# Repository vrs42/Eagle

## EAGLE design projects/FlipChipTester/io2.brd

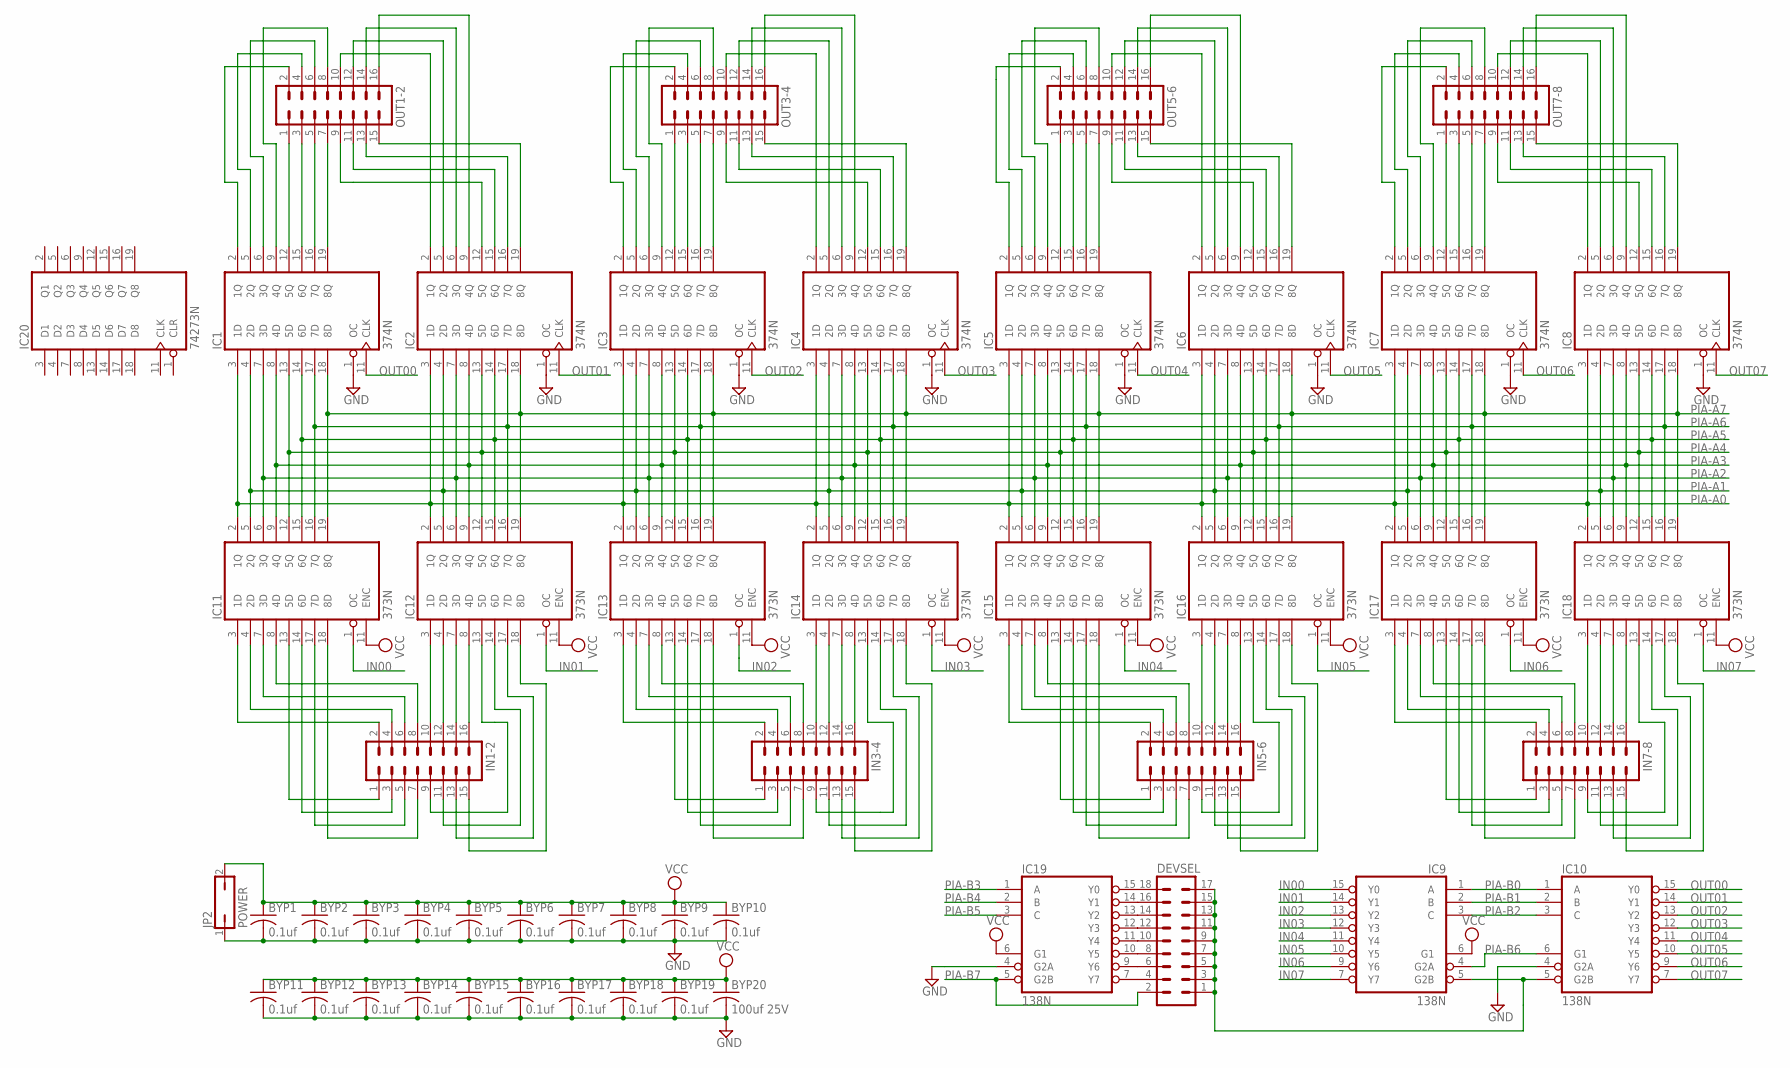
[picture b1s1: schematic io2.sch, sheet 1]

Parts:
BYP1, BYP2, BYP3, BYP4, BYP5, BYP6, BYP7, BYP8, BYP9, BYP10, BYP11, BYP12, BYP13, BYP14, BYP15, BYP16, BYP17, BYP18, BYP19: 0.1uf; C050-025X075
BYP20: 100uf 25V; C150-064X183
DEVSEL: MA09-2
IC1, IC2, IC3, IC4, IC5, IC6, IC7, IC8: 374N; DIL20
IC9, IC10, IC19: 138N; DIL16
IC11, IC12, IC13, IC14, IC15, IC16, IC17, IC18: 373N; DIL20
IC20: 74273N; DIL20
IN1-2, IN3-4, IN5-6, IN7-8: MA08-2
JP2: POWER; JP1
OUT1-2, OUT3-4, OUT5-6, OUT7-8: MA08-2

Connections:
GND: BYP1.2, BYP2.2, BYP3.2, BYP4.2, BYP5.2, BYP6.2, BYP7.2, BYP8.2, BYP9.2, BYP10.2, BYP11.2, BYP12.2, BYP13.2, BYP14.2, BYP15.2, BYP16.2, BYP17.2, BYP18.2, BYP19.2, BYP20.2, IC1.1 (OC), IC1.10 (GND), IC2.1 (OC), IC2.10 (GND), IC3.1 (OC), IC3.10 (GND), IC4.1 (OC), IC4.10 (GND), IC5.1 (OC), IC5.10 (GND), IC6.1 (OC), IC6.10 (GND), IC7.1 (OC), IC7.10 (GND), IC8.1 (OC), IC8.10 (GND), IC9.8 (GND), IC10.4 (G2A), IC10.8 (GND), IC11.10 (GND), IC12.10 (GND), IC13.10 (GND), IC14.10 (GND), IC15.10 (GND), IC16.10 (GND), IC17.10 (GND), IC18.10 (GND), IC19.4 (G2A), IC19.8 (GND), IC20.10 (GND), JP2.1; also elsewhere on the board
IN00: IC9.15 (Y0), IC11.1 (OC)
IN01: IC9.14 (Y1), IC12.1 (OC)
IN02: IC9.13 (Y2), IC13.1 (OC)
IN03: IC9.12 (Y3), IC14.1 (OC)
IN04: IC9.11 (Y4), IC15.1 (OC)
IN05: IC9.10 (Y5), IC16.1 (OC)
IN06: IC9.9 (Y6), IC17.1 (OC)
IN07: IC9.7 (Y7), IC18.1 (OC)
unnamed: IC12.3 (1D), IN1-2.10
unnamed: IC12.4 (2D), IN1-2.12
unnamed: DEVSEL.18, IC19.15 (Y0)
unnamed: DEVSEL.16, IC19.14 (Y1)
unnamed: DEVSEL.14, IC19.13 (Y2)
unnamed: DEVSEL.12, IC19.12 (Y3)
unnamed: IC12.7 (3D), IN1-2.14
unnamed: IC12.8 (4D), IN1-2.16
unnamed: IC11.8 (4D), IN1-2.8
unnamed: IC11.7 (3D), IN1-2.6
unnamed: IC11.4 (2D), IN1-2.4
unnamed: IC11.3 (1D), IN1-2.2
unnamed: IC11.13 (5D), IN1-2.1
unnamed: IC11.14 (6D), IN1-2.3
unnamed: IC11.17 (7D), IN1-2.5
unnamed: IC11.18 (8D), IN1-2.7
unnamed: IC12.13 (5D), IN1-2.9
unnamed: IC12.14 (6D), IN1-2.11
unnamed: IC12.17 (7D), IN1-2.13
unnamed: IC12.18 (8D), IN1-2.15
unnamed: DEVSEL.10, IC19.11 (Y4)
unnamed: DEVSEL.8, IC19.10 (Y5)
unnamed: DEVSEL.6, IC19.9 (Y6)
unnamed: DEVSEL.4, IC19.7 (Y7)
unnamed: DEVSEL.1, DEVSEL.3, DEVSEL.5, DEVSEL.7, DEVSEL.9, DEVSEL.11, DEVSEL.13, DEVSEL.15, DEVSEL.17, IC9.5 (G2B), IC10.5 (G2B)
unnamed: IC5.2 (1Q), OUT5-6.2
unnamed: IC18.8 (4D), IN7-8.16
unnamed: IC18.3 (1D), IN7-8.10
unnamed: IC14.3 (1D), IN3-4.10
unnamed: IC14.4 (2D), IN3-4.12
unnamed: IC14.7 (3D), IN3-4.14
unnamed: IC14.8 (4D), IN3-4.16
unnamed: IC3.12 (5Q), OUT3-4.1
unnamed: IC3.15 (6Q), OUT3-4.3
unnamed: IC3.16 (7Q), OUT3-4.5
unnamed: IC3.19 (8Q), OUT3-4.7
unnamed: IC13.3 (1D), IN3-4.2
unnamed: IC13.4 (2D), IN3-4.4
unnamed: IC13.7 (3D), IN3-4.6
unnamed: IC13.8 (4D), IN3-4.8
unnamed: IC14.13 (5D), IN3-4.9
unnamed: IC14.14 (6D), IN3-4.11
unnamed: IC14.17 (7D), IN3-4.13
unnamed: IC14.18 (8D), IN3-4.15
unnamed: IC13.13 (5D), IN3-4.1
unnamed: IC13.14 (6D), IN3-4.3
unnamed: IC13.17 (7D), IN3-4.5
unnamed: IC13.18 (8D), IN3-4.7
unnamed: IC3.5 (2Q), OUT3-4.4
unnamed: IC3.6 (3Q), OUT3-4.6
unnamed: IC3.2 (1Q), OUT3-4.2
unnamed: IC3.9 (4Q), OUT3-4.8
unnamed: IC1.12 (5Q), OUT1-2.1
unnamed: IC1.15 (6Q), OUT1-2.3
unnamed: IC1.16 (7Q), OUT1-2.5
unnamed: IC1.19 (8Q), OUT1-2.7
unnamed: IC1.2 (1Q), OUT1-2.2
unnamed: IC1.5 (2Q), OUT1-2.4
unnamed: IC1.6 (3Q), OUT1-2.6
unnamed: IC1.9 (4Q), OUT1-2.8
unnamed: IC2.19 (8Q), OUT1-2.15
unnamed: IC2.16 (7Q), OUT1-2.13
unnamed: IC2.15 (6Q), OUT1-2.11
unnamed: IC2.12 (5Q), OUT1-2.9
unnamed: IC2.2 (1Q), OUT1-2.10
unnamed: IC2.5 (2Q), OUT1-2.12
unnamed: IC2.6 (3Q), OUT1-2.14
unnamed: IC2.9 (4Q), OUT1-2.16
unnamed: IC4.2 (1Q), OUT3-4.10
unnamed: IC4.5 (2Q), OUT3-4.12
unnamed: IC4.6 (3Q), OUT3-4.14
unnamed: IC4.9 (4Q), OUT3-4.16
unnamed: IC4.19 (8Q), OUT3-4.15
unnamed: IC4.16 (7Q), OUT3-4.13
unnamed: IC4.15 (6Q), OUT3-4.11
unnamed: IC4.12 (5Q), OUT3-4.9
unnamed: IC16.3 (1D), IN5-6.10
unnamed: IC16.4 (2D), IN5-6.12
unnamed: IC16.7 (3D), IN5-6.14
unnamed: IC16.8 (4D), IN5-6.16
unnamed: IC5.12 (5Q), OUT5-6.1
unnamed: IC5.15 (6Q), OUT5-6.3
unnamed: IC5.16 (7Q), OUT5-6.5
unnamed: IC5.19 (8Q), OUT5-6.7
unnamed: IC7.12 (5Q), OUT7-8.1
unnamed: IC7.15 (6Q), OUT7-8.3
unnamed: IC7.16 (7Q), OUT7-8.5
unnamed: IC7.19 (8Q), OUT7-8.7
unnamed: IC5.5 (2Q), OUT5-6.4
unnamed: IC5.6 (3Q), OUT5-6.6
unnamed: IC5.9 (4Q), OUT5-6.8
unnamed: IC6.12 (5Q), OUT5-6.9
unnamed: IC6.15 (6Q), OUT5-6.11
unnamed: IC18.4 (2D), IN7-8.12
unnamed: IC6.16 (7Q), OUT5-6.13
unnamed: IC6.19 (8Q), OUT5-6.15
unnamed: IC6.2 (1Q), OUT5-6.10
unnamed: IC6.5 (2Q), OUT5-6.12
unnamed: IC6.6 (3Q), OUT5-6.14
unnamed: IC6.9 (4Q), OUT5-6.16
unnamed: IC15.3 (1D), IN5-6.2
unnamed: IC15.4 (2D), IN5-6.4
unnamed: IC15.7 (3D), IN5-6.6
unnamed: IC15.8 (4D), IN5-6.8
unnamed: IC16.13 (5D), IN5-6.9
unnamed: IC16.14 (6D), IN5-6.11
unnamed: IC16.17 (7D), IN5-6.13
unnamed: IC16.18 (8D), IN5-6.15
unnamed: IC15.13 (5D), IN5-6.1
unnamed: IC15.14 (6D), IN5-6.3
unnamed: IC15.17 (7D), IN5-6.5
unnamed: IC15.18 (8D), IN5-6.7
unnamed: IC8.19 (8Q), OUT7-8.15
unnamed: IC8.16 (7Q), OUT7-8.13
unnamed: IC8.15 (6Q), OUT7-8.11
unnamed: IC8.12 (5Q), OUT7-8.9
unnamed: IC8.2 (1Q), OUT7-8.10
unnamed: IC8.5 (2Q), OUT7-8.12
unnamed: IC8.6 (3Q), OUT7-8.14
unnamed: IC8.9 (4Q), OUT7-8.16
unnamed: IC7.9 (4Q), OUT7-8.8
unnamed: IC7.6 (3Q), OUT7-8.6
unnamed: IC7.5 (2Q), OUT7-8.4
unnamed: IC18.7 (3D), IN7-8.14
unnamed: IC18.13 (5D), IN7-8.9
unnamed: IC18.14 (6D), IN7-8.11
unnamed: IC18.17 (7D), IN7-8.13
unnamed: IC18.18 (8D), IN7-8.15
unnamed: IC17.3 (1D), IN7-8.2
unnamed: IC17.4 (2D), IN7-8.4
unnamed: IC17.7 (3D), IN7-8.6
unnamed: IC17.8 (4D), IN7-8.8
unnamed: IC17.13 (5D), IN7-8.1
unnamed: IC17.14 (6D), IN7-8.3
unnamed: IC17.17 (7D), IN7-8.5
unnamed: IC17.18 (8D), IN7-8.7
unnamed: IC7.2 (1Q), OUT7-8.2
OUT00: IC1.11 (CLK), IC10.15 (Y0)
OUT01: IC2.11 (CLK), IC10.14 (Y1)
OUT02: IC3.11 (CLK), IC10.13 (Y2)
OUT03: IC4.11 (CLK), IC10.12 (Y3)
OUT04: IC5.11 (CLK), IC10.11 (Y4)
OUT05: IC6.11 (CLK), IC10.10 (Y5)
OUT06: IC7.11 (CLK), IC10.9 (Y6)
OUT07: IC8.11 (CLK), IC10.7 (Y7)
PIA-A0: IC1.3 (1D), IC2.3 (1D), IC3.3 (1D), IC4.3 (1D), IC5.3 (1D), IC6.3 (1D), IC7.3 (1D), IC8.3 (1D), IC11.2 (1Q), IC12.2 (1Q), IC13.2 (1Q), IC14.2 (1Q), IC15.2 (1Q), IC16.2 (1Q), IC17.2 (1Q), IC18.2 (1Q); also elsewhere on the board
PIA-A1: IC1.4 (2D), IC2.4 (2D), IC3.4 (2D), IC4.4 (2D), IC5.4 (2D), IC6.4 (2D), IC7.4 (2D), IC8.4 (2D), IC11.5 (2Q), IC12.5 (2Q), IC13.5 (2Q), IC14.5 (2Q), IC15.5 (2Q), IC16.5 (2Q), IC17.5 (2Q), IC18.5 (2Q); also elsewhere on the board
PIA-A2: IC1.7 (3D), IC2.7 (3D), IC3.7 (3D), IC4.7 (3D), IC5.7 (3D), IC6.7 (3D), IC7.7 (3D), IC8.7 (3D), IC11.6 (3Q), IC12.6 (3Q), IC13.6 (3Q), IC14.6 (3Q), IC15.6 (3Q), IC16.6 (3Q), IC17.6 (3Q), IC18.6 (3Q); also elsewhere on the board
PIA-A3: IC1.8 (4D), IC2.8 (4D), IC3.8 (4D), IC4.8 (4D), IC5.8 (4D), IC6.8 (4D), IC7.8 (4D), IC8.8 (4D), IC11.9 (4Q), IC12.9 (4Q), IC13.9 (4Q), IC14.9 (4Q), IC15.9 (4Q), IC16.9 (4Q), IC17.9 (4Q), IC18.9 (4Q); also elsewhere on the board
PIA-A4: IC1.13 (5D), IC2.13 (5D), IC3.13 (5D), IC4.13 (5D), IC5.13 (5D), IC6.13 (5D), IC7.13 (5D), IC8.13 (5D), IC11.12 (5Q), IC12.12 (5Q), IC13.12 (5Q), IC14.12 (5Q), IC15.12 (5Q), IC16.12 (5Q), IC17.12 (5Q), IC18.12 (5Q); also elsewhere on the board
PIA-A5: IC1.14 (6D), IC2.14 (6D), IC3.14 (6D), IC4.14 (6D), IC5.14 (6D), IC6.14 (6D), IC7.14 (6D), IC8.14 (6D), IC11.15 (6Q), IC12.15 (6Q), IC13.15 (6Q), IC14.15 (6Q), IC15.15 (6Q), IC16.15 (6Q), IC17.15 (6Q), IC18.15 (6Q); also elsewhere on the board
PIA-A6: IC1.17 (7D), IC2.17 (7D), IC3.17 (7D), IC4.17 (7D), IC5.17 (7D), IC6.17 (7D), IC7.17 (7D), IC8.17 (7D), IC11.16 (7Q), IC12.16 (7Q), IC13.16 (7Q), IC14.16 (7Q), IC15.16 (7Q), IC16.16 (7Q), IC17.16 (7Q), IC18.16 (7Q); also elsewhere on the board
PIA-A7: IC1.18 (8D), IC2.18 (8D), IC3.18 (8D), IC4.18 (8D), IC5.18 (8D), IC6.18 (8D), IC7.18 (8D), IC8.18 (8D), IC11.19 (8Q), IC12.19 (8Q), IC13.19 (8Q), IC14.19 (8Q), IC15.19 (8Q), IC16.19 (8Q), IC17.19 (8Q), IC18.19 (8Q); also elsewhere on the board
PIA-B0: IC9.1 (A), IC10.1 (A); also elsewhere on the board
PIA-B1: IC9.2 (B), IC10.2 (B); also elsewhere on the board
PIA-B2: IC9.3 (C), IC10.3 (C); also elsewhere on the board
PIA-B3: IC19.1 (A); also elsewhere on the board
PIA-B4: IC19.2 (B); also elsewhere on the board
PIA-B5: IC19.3 (C); also elsewhere on the board
PIA-B6: IC9.4 (G2A), IC10.6 (G1); also elsewhere on the board
PIA-B7: DEVSEL.2, IC19.5 (G2B); also elsewhere on the board
VCC: BYP1.1, BYP2.1, BYP3.1, BYP4.1, BYP5.1, BYP6.1, BYP7.1, BYP8.1, BYP9.1, BYP10.1, BYP11.1, BYP12.1, BYP13.1, BYP14.1, BYP15.1, BYP16.1, BYP17.1, BYP18.1, BYP19.1, BYP20.1, IC1.20 (VCC), IC2.20 (VCC), IC3.20 (VCC), IC4.20 (VCC), IC5.20 (VCC), IC6.20 (VCC), IC7.20 (VCC), IC8.20 (VCC), IC9.6 (G1), IC9.16 (VCC), IC10.16 (VCC), IC11.11 (ENC), IC11.20 (VCC), IC12.11 (ENC), IC12.20 (VCC), IC13.11 (ENC), IC13.20 (VCC), IC14.11 (ENC), IC14.20 (VCC), IC15.11 (ENC), IC15.20 (VCC), IC16.11 (ENC), IC16.20 (VCC), IC17.11 (ENC), IC17.20 (VCC), IC18.11 (ENC), IC18.20 (VCC), IC19.6 (G1), IC19.16 (VCC), IC20.20 (VCC), JP2.2; also elsewhere on the board

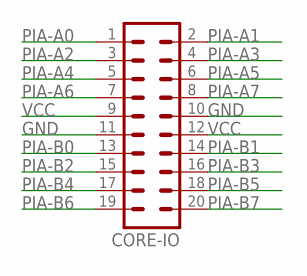
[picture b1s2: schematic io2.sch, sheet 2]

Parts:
CORE-IO: MA10-2

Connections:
GND: CORE-IO.10, CORE-IO.11; also elsewhere on the board
PIA-A0: CORE-IO.1; also elsewhere on the board
PIA-A1: CORE-IO.2; also elsewhere on the board
PIA-A2: CORE-IO.3; also elsewhere on the board
PIA-A3: CORE-IO.4; also elsewhere on the board
PIA-A4: CORE-IO.5; also elsewhere on the board
PIA-A5: CORE-IO.6; also elsewhere on the board
PIA-A6: CORE-IO.7; also elsewhere on the board
PIA-A7: CORE-IO.8; also elsewhere on the board
PIA-B0: CORE-IO.13; also elsewhere on the board
PIA-B1: CORE-IO.14; also elsewhere on the board
PIA-B2: CORE-IO.15; also elsewhere on the board
PIA-B3: CORE-IO.16; also elsewhere on the board
PIA-B4: CORE-IO.17; also elsewhere on the board
PIA-B5: CORE-IO.18; also elsewhere on the board
PIA-B6: CORE-IO.19; also elsewhere on the board
PIA-B7: CORE-IO.20; also elsewhere on the board
VCC: CORE-IO.9, CORE-IO.12; also elsewhere on the board

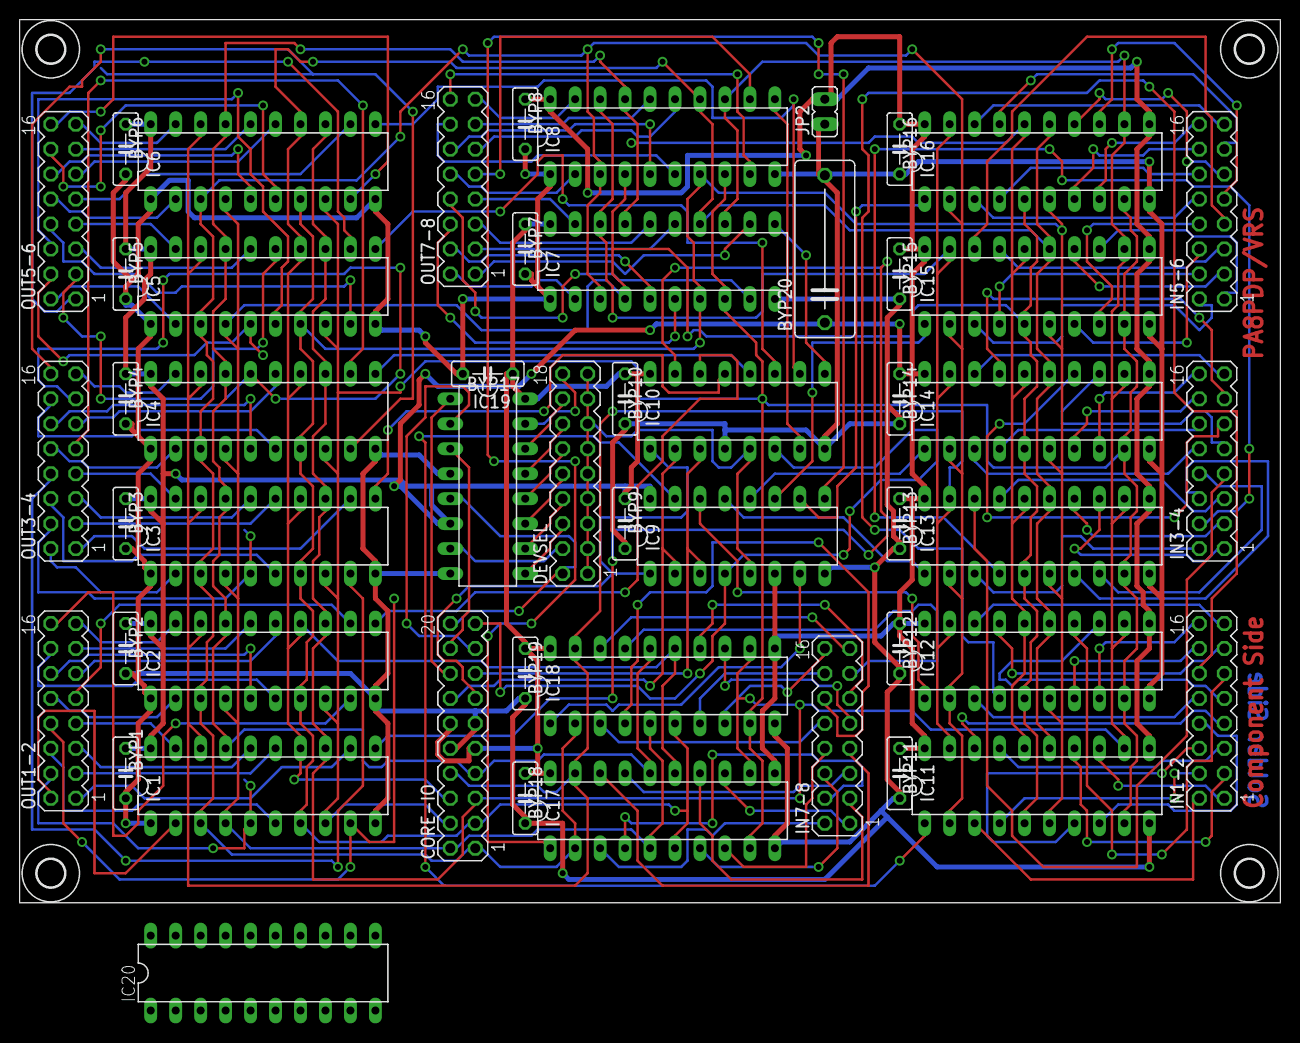
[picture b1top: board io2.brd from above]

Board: 2 copper layers, 128.2 x 89.8 mm, 55 parts (0 on the bottom side), 171 nets.

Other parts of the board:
U$1, U$2, U$3, U$4: 2,8

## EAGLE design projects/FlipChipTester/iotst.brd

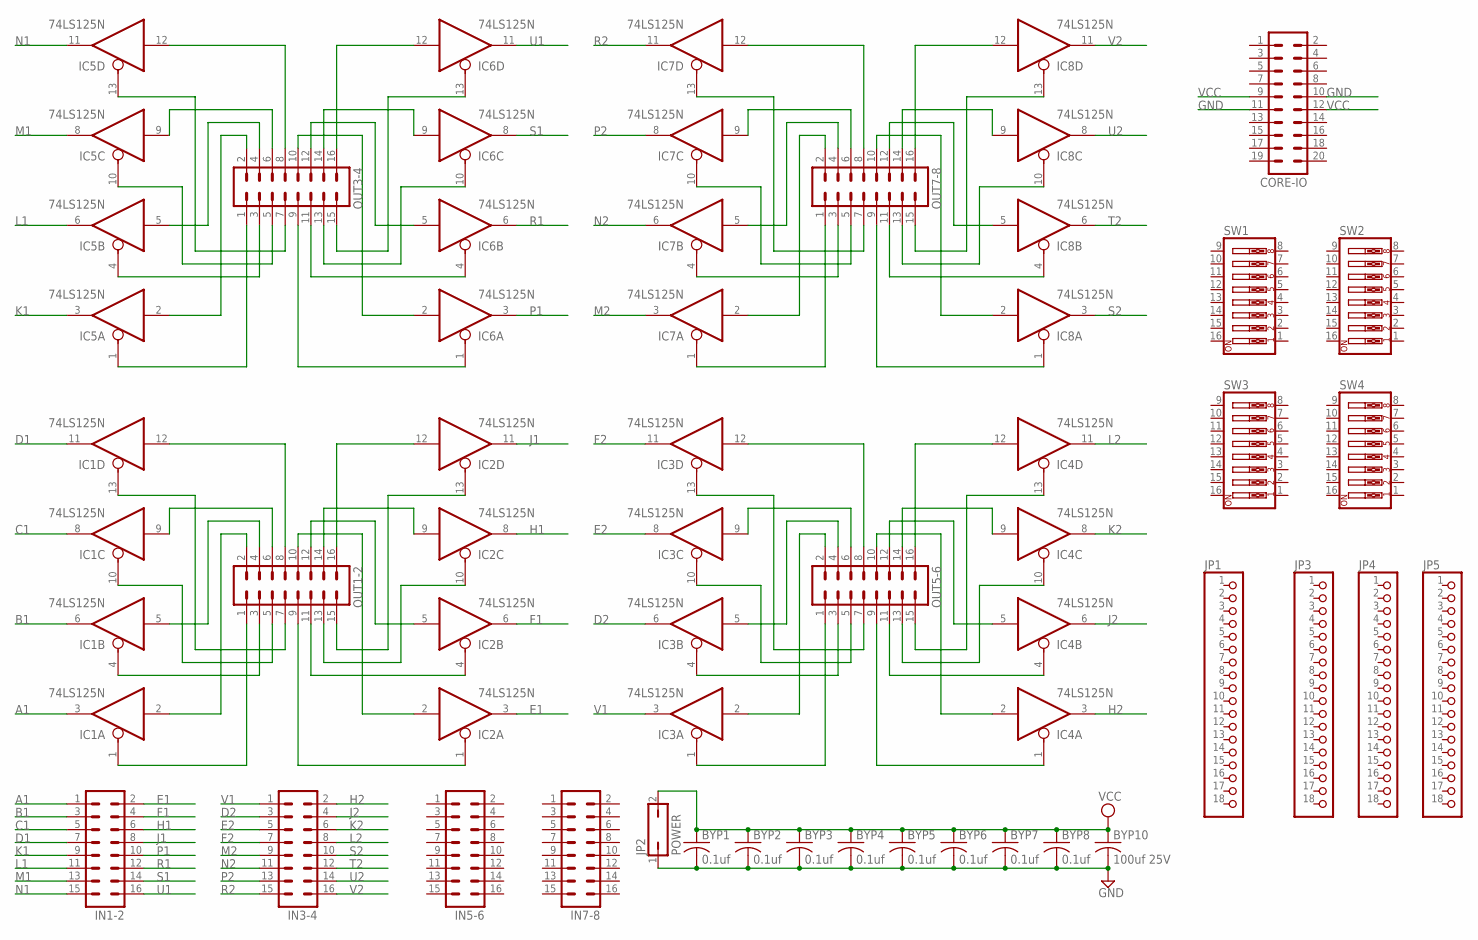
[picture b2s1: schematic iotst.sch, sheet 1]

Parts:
BYP1, BYP2, BYP3, BYP4, BYP5, BYP6, BYP7, BYP8: 0.1uf; C050-025X075
BYP10: 100uf 25V; C150-064X183
CORE-IO: MA10-2
IC1, IC2, IC3, IC4, IC5, IC6, IC7, IC8: 74LS125N; DIL14
IN1-2, IN3-4, IN5-6, IN7-8: MA08-2
JP1, JP3, JP4, JP5: PINHD-1X18; 1X18
JP2: POWER; JP1
OUT1-2, OUT3-4, OUT5-6, OUT7-8: MA08-2
SW1, SW2, SW3, SW4: SW_DIP-8; EDG-08

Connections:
A1: IC1.3 (O), IN1-2.1; also elsewhere on the board
B1: IC1.6 (O), IN1-2.3; also elsewhere on the board
C1: IC1.8 (O), IN1-2.5; also elsewhere on the board
D1: IC1.11 (O), IN1-2.7; also elsewhere on the board
D2: IC3.6 (O), IN3-4.3; also elsewhere on the board
E1: IC2.3 (O), IN1-2.2; also elsewhere on the board
E2: IC3.8 (O), IN3-4.5; also elsewhere on the board
F1: IC2.6 (O), IN1-2.4; also elsewhere on the board
F2: IC3.11 (O), IN3-4.7; also elsewhere on the board
GND: BYP1.2, BYP2.2, BYP3.2, BYP4.2, BYP5.2, BYP6.2, BYP7.2, BYP8.2, BYP10.2, CORE-IO.10, CORE-IO.11, IC1.7 (GND), IC2.7 (GND), IC3.7 (GND), IC4.7 (GND), IC5.7 (GND), IC6.7 (GND), IC7.7 (GND), IC8.7 (GND), JP2.1; also elsewhere on the board
H1: IC2.8 (O), IN1-2.6; also elsewhere on the board
H2: IC4.3 (O), IN3-4.2; also elsewhere on the board
J1: IC2.11 (O), IN1-2.8; also elsewhere on the board
J2: IC4.6 (O), IN3-4.4; also elsewhere on the board
K1: IC5.3 (O), IN1-2.9; also elsewhere on the board
K2: IC4.8 (O), IN3-4.6; also elsewhere on the board
L1: IC5.6 (O), IN1-2.11; also elsewhere on the board
L2: IC4.11 (O), IN3-4.8; also elsewhere on the board
M1: IC5.8 (O), IN1-2.13; also elsewhere on the board
M2: IC7.3 (O), IN3-4.9; also elsewhere on the board
N1: IC5.11 (O), IN1-2.15; also elsewhere on the board
N2: IC7.6 (O), IN3-4.11; also elsewhere on the board
unnamed: IC1.1 (OE), OUT1-2.1
unnamed: IC1.4 (OE), OUT1-2.3
unnamed: IC1.10 (OE), OUT1-2.5
unnamed: IC1.13 (OE), OUT1-2.7
unnamed: IC1.2 (I), OUT1-2.2
unnamed: IC1.5 (I), OUT1-2.4
unnamed: IC1.9 (I), OUT1-2.6
unnamed: IC1.12 (I), OUT1-2.8
unnamed: IC3.4 (OE), OUT5-6.3
unnamed: IC2.10 (OE), OUT1-2.13
unnamed: IC2.4 (OE), OUT1-2.11
unnamed: IC2.1 (OE), OUT1-2.9
unnamed: IC2.2 (I), OUT1-2.10
unnamed: IC2.5 (I), OUT1-2.12
unnamed: IC2.9 (I), OUT1-2.14
unnamed: IC2.12 (I), OUT1-2.16
unnamed: IC3.13 (OE), OUT5-6.7
unnamed: IC2.13 (OE), OUT1-2.15
unnamed: IC3.2 (I), OUT5-6.2
unnamed: IC3.5 (I), OUT5-6.4
unnamed: IC3.9 (I), OUT5-6.6
unnamed: IC3.12 (I), OUT5-6.8
unnamed: IC4.10 (OE), OUT5-6.13
unnamed: IC4.4 (OE), OUT5-6.11
unnamed: IC4.1 (OE), OUT5-6.9
unnamed: IC4.2 (I), OUT5-6.10
unnamed: IC4.9 (I), OUT5-6.14
unnamed: IC4.12 (I), OUT5-6.16
unnamed: IC3.1 (OE), OUT5-6.1
unnamed: IC3.10 (OE), OUT5-6.5
unnamed: IC4.5 (I), OUT5-6.12
unnamed: IC4.13 (OE), OUT5-6.15
unnamed: IC5.4 (OE), OUT3-4.3
unnamed: IC5.13 (OE), OUT3-4.7
unnamed: IC5.2 (I), OUT3-4.2
unnamed: IC5.5 (I), OUT3-4.4
unnamed: IC5.9 (I), OUT3-4.6
unnamed: IC5.12 (I), OUT3-4.8
unnamed: IC6.10 (OE), OUT3-4.13
unnamed: IC6.4 (OE), OUT3-4.11
unnamed: IC6.1 (OE), OUT3-4.9
unnamed: IC6.2 (I), OUT3-4.10
unnamed: IC6.9 (I), OUT3-4.14
unnamed: IC6.12 (I), OUT3-4.16
unnamed: IC5.1 (OE), OUT3-4.1
unnamed: IC5.10 (OE), OUT3-4.5
unnamed: IC6.5 (I), OUT3-4.12
unnamed: IC6.13 (OE), OUT3-4.15
unnamed: IC7.4 (OE), OUT7-8.3
unnamed: IC7.13 (OE), OUT7-8.7
unnamed: IC7.2 (I), OUT7-8.2
unnamed: IC7.5 (I), OUT7-8.4
unnamed: IC7.9 (I), OUT7-8.6
unnamed: IC7.12 (I), OUT7-8.8
unnamed: IC8.10 (OE), OUT7-8.13
unnamed: IC8.4 (OE), OUT7-8.11
unnamed: IC8.1 (OE), OUT7-8.9
unnamed: IC8.2 (I), OUT7-8.10
unnamed: IC8.9 (I), OUT7-8.14
unnamed: IC8.12 (I), OUT7-8.16
unnamed: IC7.1 (OE), OUT7-8.1
unnamed: IC7.10 (OE), OUT7-8.5
unnamed: IC8.5 (I), OUT7-8.12
unnamed: IC8.13 (OE), OUT7-8.15
P1: IC6.3 (O), IN1-2.10; also elsewhere on the board
P2: IC7.8 (O), IN3-4.13; also elsewhere on the board
R1: IC6.6 (O), IN1-2.12; also elsewhere on the board
R2: IC7.11 (O), IN3-4.15; also elsewhere on the board
S1: IC6.8 (O), IN1-2.14; also elsewhere on the board
S2: IC8.3 (O), IN3-4.10; also elsewhere on the board
T2: IC8.6 (O), IN3-4.12; also elsewhere on the board
U1: IC6.11 (O), IN1-2.16; also elsewhere on the board
U2: IC8.8 (O), IN3-4.14; also elsewhere on the board
V1: IC3.3 (O), IN3-4.1; also elsewhere on the board
V2: IC8.11 (O), IN3-4.16; also elsewhere on the board
VCC: BYP1.1, BYP2.1, BYP3.1, BYP4.1, BYP5.1, BYP6.1, BYP7.1, BYP8.1, BYP10.1, CORE-IO.9, CORE-IO.12, IC1.14 (VCC), IC2.14 (VCC), IC3.14 (VCC), IC4.14 (VCC), IC5.14 (VCC), IC6.14 (VCC), IC7.14 (VCC), IC8.14 (VCC), JP2.2; also elsewhere on the board

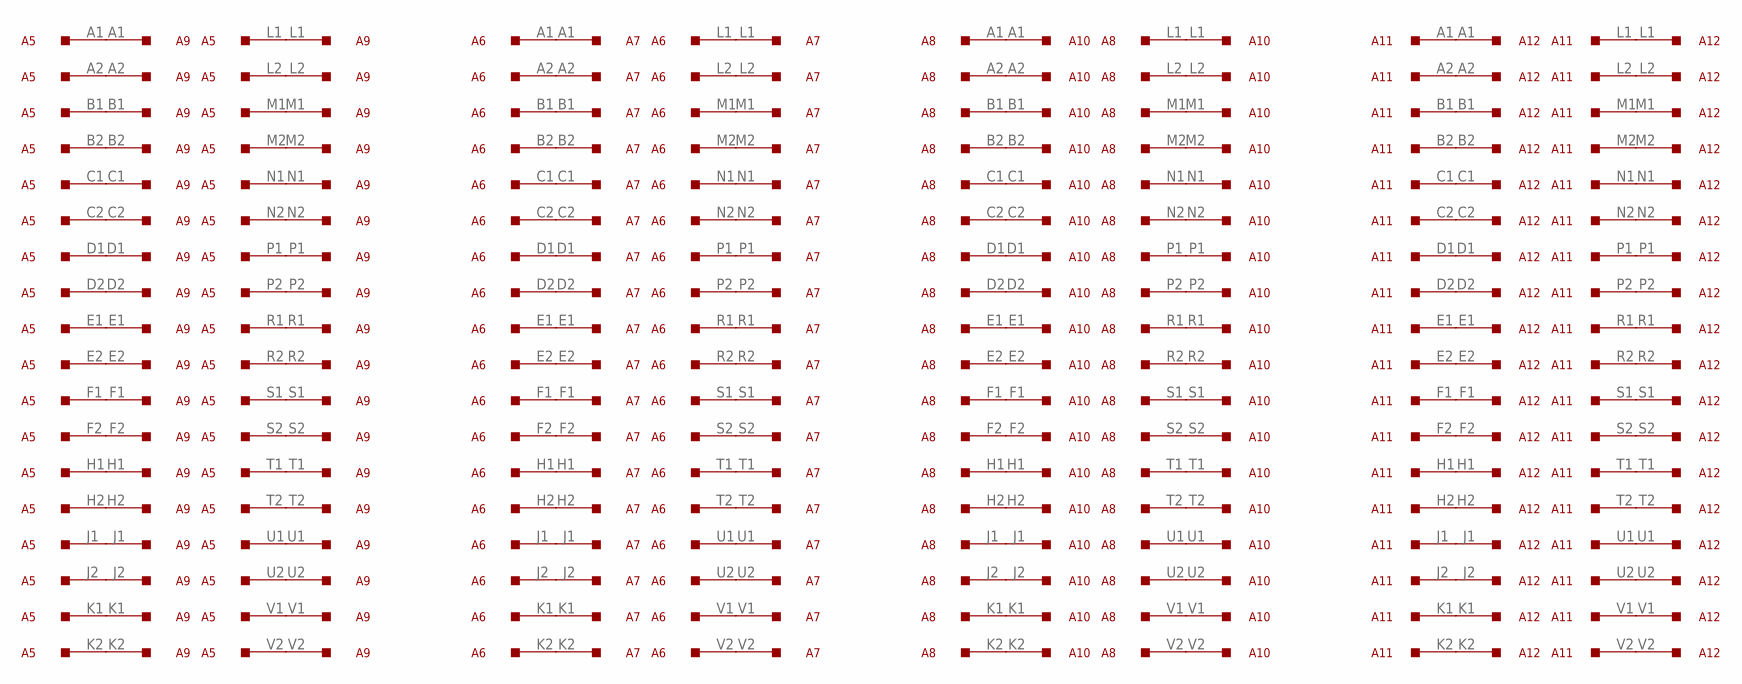
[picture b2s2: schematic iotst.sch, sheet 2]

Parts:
A5, A6, A7, A8, A9, A10, A11, A12: M916; H807

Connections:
unnamed: A5.L1, A9.L1
unnamed: A5.L2, A9.L2
unnamed: A5.M1, A9.M1
unnamed: A5.M2, A9.M2
unnamed: A5.N1, A9.N1
unnamed: A5.N2, A9.N2
unnamed: A5.P1, A9.P1
unnamed: A5.P2, A9.P2
unnamed: A5.R1, A9.R1
unnamed: A5.R2, A9.R2
unnamed: A5.S1, A9.S1
unnamed: A5.S2, A9.S2
unnamed: A5.T1, A9.T1
unnamed: A5.T2, A9.T2
unnamed: A5.U1, A9.U1
unnamed: A5.U2, A9.U2
unnamed: A5.V1, A9.V1
unnamed: A5.V2, A9.V2
unnamed: A5.A1, A9.A1
unnamed: A5.A2, A9.A2
unnamed: A5.B1, A9.B1
unnamed: A5.B2, A9.B2
unnamed: A5.C1, A9.C1
unnamed: A5.C2, A9.C2
unnamed: A5.D1, A9.D1
unnamed: A5.D2, A9.D2
unnamed: A5.E1, A9.E1
unnamed: A5.E2, A9.E2
unnamed: A5.F1, A9.F1
unnamed: A5.F2, A9.F2
unnamed: A5.H1, A9.H1
unnamed: A5.H2, A9.H2
unnamed: A5.J1, A9.J1
unnamed: A5.J2, A9.J2
unnamed: A5.K1, A9.K1
unnamed: A5.K2, A9.K2
unnamed: A6.L1, A7.L1
unnamed: A6.L2, A7.L2
unnamed: A6.M1, A7.M1
unnamed: A6.M2, A7.M2
unnamed: A6.N1, A7.N1
unnamed: A6.N2, A7.N2
unnamed: A6.P1, A7.P1
unnamed: A6.P2, A7.P2
unnamed: A6.R1, A7.R1
unnamed: A6.R2, A7.R2
unnamed: A6.S1, A7.S1
unnamed: A6.S2, A7.S2
unnamed: A6.T1, A7.T1
unnamed: A6.T2, A7.T2
unnamed: A6.U1, A7.U1
unnamed: A6.U2, A7.U2
unnamed: A6.V1, A7.V1
unnamed: A6.V2, A7.V2
unnamed: A6.A1, A7.A1
unnamed: A6.A2, A7.A2
unnamed: A6.B1, A7.B1
unnamed: A6.B2, A7.B2
unnamed: A6.C1, A7.C1
unnamed: A6.C2, A7.C2
unnamed: A6.D1, A7.D1
unnamed: A6.D2, A7.D2
unnamed: A6.E1, A7.E1
unnamed: A6.E2, A7.E2
unnamed: A6.F1, A7.F1
unnamed: A6.F2, A7.F2
unnamed: A6.H1, A7.H1
unnamed: A6.H2, A7.H2
unnamed: A6.J1, A7.J1
unnamed: A6.J2, A7.J2
unnamed: A6.K1, A7.K1
unnamed: A6.K2, A7.K2
unnamed: A8.L1, A10.L1
unnamed: A8.L2, A10.L2
unnamed: A8.M1, A10.M1
unnamed: A8.M2, A10.M2
unnamed: A8.N1, A10.N1
unnamed: A8.N2, A10.N2
unnamed: A8.P1, A10.P1
unnamed: A8.P2, A10.P2
unnamed: A8.R1, A10.R1
unnamed: A8.R2, A10.R2
unnamed: A8.S1, A10.S1
unnamed: A8.S2, A10.S2
unnamed: A8.T1, A10.T1
unnamed: A8.T2, A10.T2
unnamed: A8.U1, A10.U1
unnamed: A8.U2, A10.U2
unnamed: A8.V1, A10.V1
unnamed: A8.V2, A10.V2
unnamed: A8.A1, A10.A1
unnamed: A8.A2, A10.A2
unnamed: A8.B1, A10.B1
unnamed: A8.B2, A10.B2
unnamed: A8.C1, A10.C1
unnamed: A8.C2, A10.C2
unnamed: A8.D1, A10.D1
unnamed: A8.D2, A10.D2
unnamed: A8.E1, A10.E1
unnamed: A8.E2, A10.E2
unnamed: A8.F1, A10.F1
unnamed: A8.F2, A10.F2
unnamed: A8.H1, A10.H1
unnamed: A8.H2, A10.H2
unnamed: A8.J1, A10.J1
unnamed: A8.J2, A10.J2
unnamed: A8.K1, A10.K1
unnamed: A8.K2, A10.K2
unnamed: A11.L1, A12.L1
unnamed: A11.L2, A12.L2
unnamed: A11.M1, A12.M1
unnamed: A11.M2, A12.M2
unnamed: A11.N1, A12.N1
unnamed: A11.N2, A12.N2
unnamed: A11.P1, A12.P1
unnamed: A11.P2, A12.P2
unnamed: A11.R1, A12.R1
unnamed: A11.R2, A12.R2
unnamed: A11.S1, A12.S1
unnamed: A11.S2, A12.S2
unnamed: A11.T1, A12.T1
unnamed: A11.T2, A12.T2
unnamed: A11.U1, A12.U1
unnamed: A11.U2, A12.U2
unnamed: A11.V1, A12.V1
unnamed: A11.V2, A12.V2
unnamed: A11.A1, A12.A1
unnamed: A11.A2, A12.A2
unnamed: A11.B1, A12.B1
unnamed: A11.B2, A12.B2
unnamed: A11.C1, A12.C1
unnamed: A11.C2, A12.C2
unnamed: A11.D1, A12.D1
unnamed: A11.D2, A12.D2
unnamed: A11.E1, A12.E1
unnamed: A11.E2, A12.E2
unnamed: A11.F1, A12.F1
unnamed: A11.F2, A12.F2
unnamed: A11.H1, A12.H1
unnamed: A11.H2, A12.H2
unnamed: A11.J1, A12.J1
unnamed: A11.J2, A12.J2
unnamed: A11.K1, A12.K1
unnamed: A11.K2, A12.K2

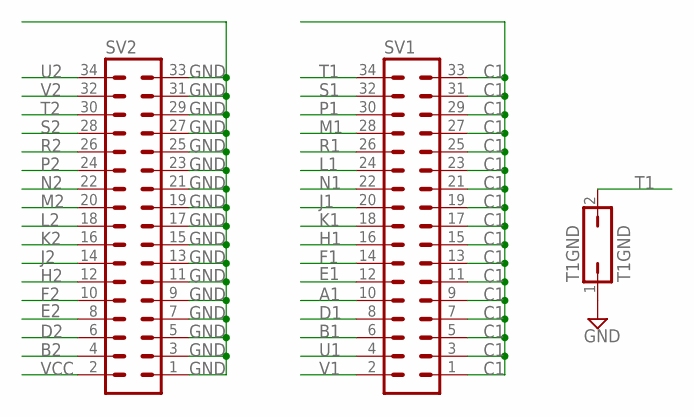
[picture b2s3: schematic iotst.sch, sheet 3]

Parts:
SV1, SV2: MA17-2
T1GND: T1GND; JP1

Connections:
A1: SV1.10; also elsewhere on the board
B1: SV1.6; also elsewhere on the board
B2: SV2.4
C1: SV1.1, SV1.3, SV1.5, SV1.7, SV1.9, SV1.11, SV1.13, SV1.15, SV1.17, SV1.19, SV1.21, SV1.23, SV1.25, SV1.27, SV1.29, SV1.31, SV1.33; also elsewhere on the board
D1: SV1.8; also elsewhere on the board
D2: SV2.6; also elsewhere on the board
E1: SV1.12; also elsewhere on the board
E2: SV2.8; also elsewhere on the board
F1: SV1.14; also elsewhere on the board
F2: SV2.10; also elsewhere on the board
GND: SV2.1, SV2.3, SV2.5, SV2.7, SV2.9, SV2.11, SV2.13, SV2.15, SV2.17, SV2.19, SV2.21, SV2.23, SV2.25, SV2.27, SV2.29, SV2.31, SV2.33, T1GND.1; also elsewhere on the board
H1: SV1.16; also elsewhere on the board
H2: SV2.12; also elsewhere on the board
J1: SV1.20; also elsewhere on the board
J2: SV2.14; also elsewhere on the board
K1: SV1.18; also elsewhere on the board
K2: SV2.16; also elsewhere on the board
L1: SV1.24; also elsewhere on the board
L2: SV2.18; also elsewhere on the board
M1: SV1.28; also elsewhere on the board
M2: SV2.20; also elsewhere on the board
N1: SV1.22; also elsewhere on the board
N2: SV2.22; also elsewhere on the board
P1: SV1.30; also elsewhere on the board
P2: SV2.24; also elsewhere on the board
R1: SV1.26; also elsewhere on the board
R2: SV2.26; also elsewhere on the board
S1: SV1.32; also elsewhere on the board
S2: SV2.28; also elsewhere on the board
T1: SV1.34, T1GND.2
T2: SV2.30; also elsewhere on the board
U1: SV1.4; also elsewhere on the board
U2: SV2.34; also elsewhere on the board
V1: SV1.2; also elsewhere on the board
V2: SV2.32; also elsewhere on the board
VCC: SV2.2; also elsewhere on the board

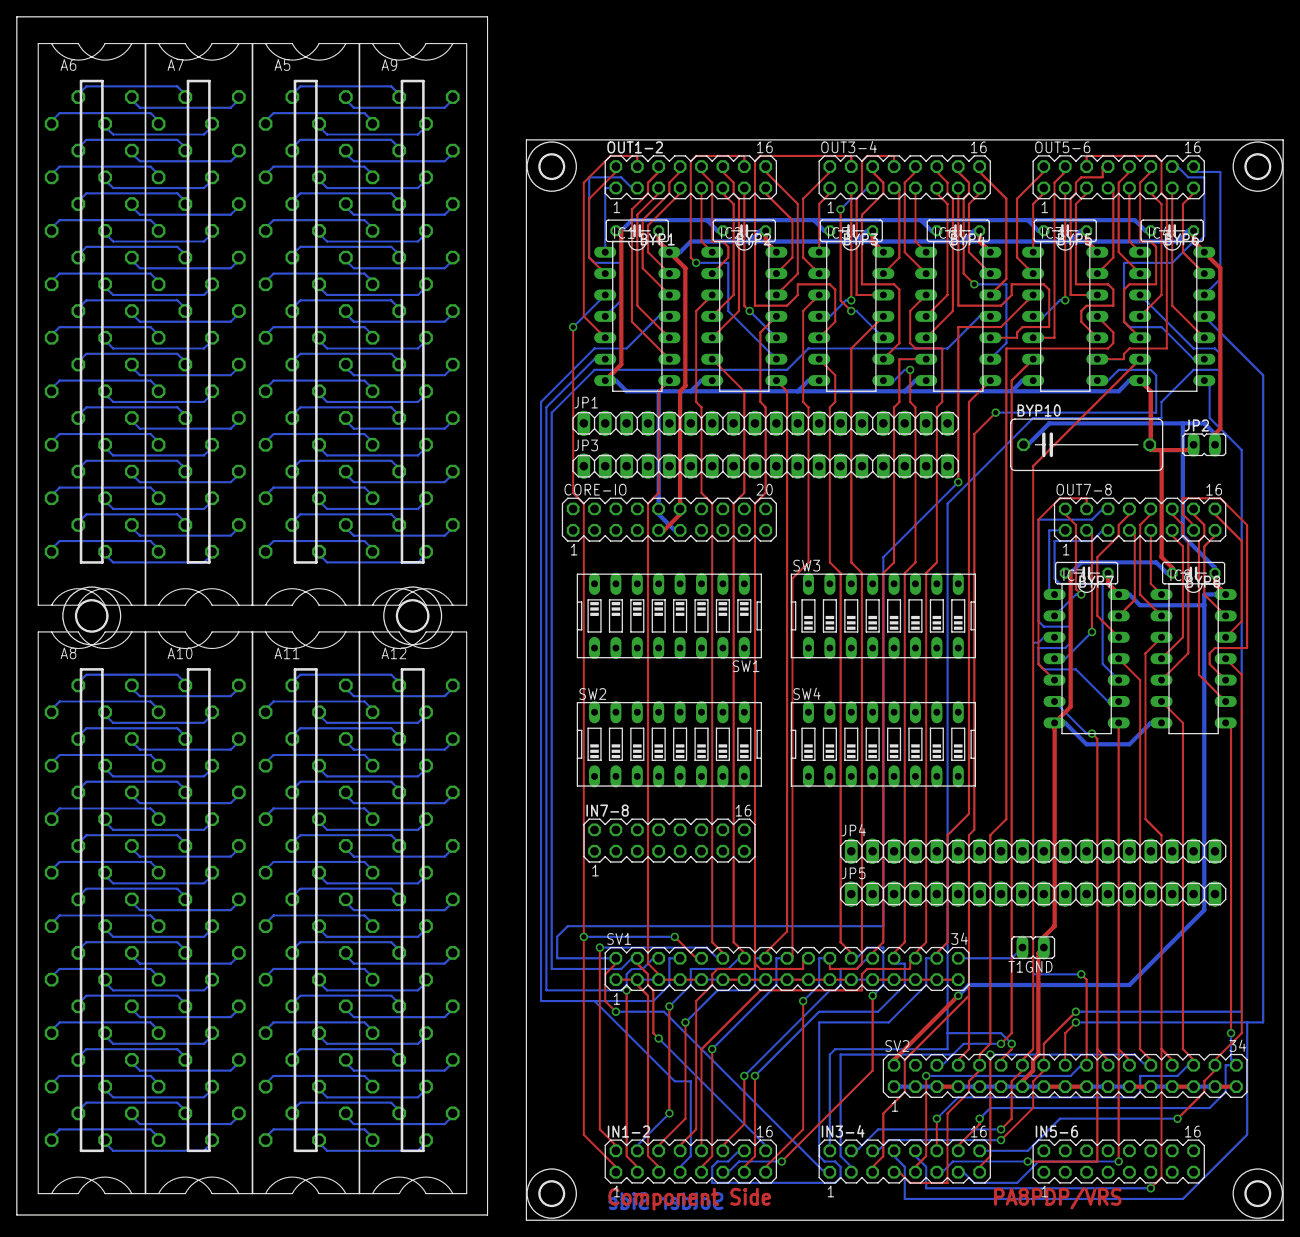
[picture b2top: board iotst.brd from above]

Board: 2 copper layers, 89.8 x 128.2 mm, 52 parts (0 on the bottom side), 243 nets.

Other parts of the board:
U$1, U$2, U$3, U$4: 2,8
U$5, U$6: 3,6
